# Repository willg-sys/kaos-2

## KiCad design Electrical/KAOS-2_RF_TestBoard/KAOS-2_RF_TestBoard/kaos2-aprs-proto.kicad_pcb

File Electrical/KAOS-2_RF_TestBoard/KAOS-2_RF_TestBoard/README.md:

# KAOS-2 RF Test Board (rev A)

Small 2-layer prototype (72 × 46 mm, 1.6 mm) to prove the 144.39 MHz APRS transmit chain and the 915 MHz LoRa link before the flight RF board. The RF MCU (Raspberry Pi Pico) stays off-board and connects through the 2×9 header J1.

## What's on it
- **144.39 MHz APRS TX:** Semtech SX1278 (direct-FSK AFSK from Pico PIO), Jauch 32 MHz TCXO, L-match to Semtech's measured PA_BOOST load (~13 + j7 Ω, AN1200.19), 7-pole 0.1 dB Chebyshev low-pass (fc ≈ 170 MHz), output pi-pad footprint, edge SMA (J3).
- **915 MHz LoRa:** Ai-Thinker Ra-01H (SX1276) with its own supply filter, pi-match footprint and a 50 Ω coplanar trace to edge SMA (J5).
- Bench 3.3 V input (J2) with current-measure jumper (JP1), test points, u.FL probe footprint (J4, DNP) between match and filter.

## Files
| File | What |
|---|---|
| `kaos2-aprs-proto.kicad_pro/.kicad_sch/.kicad_pcb` | KiCad project (KiCad 10 format) |
| `kaos2-aprs-proto.kicad_dru` | Custom DRC rule (KiCad 8+) waiving edge clearance for the edge-mount SMA pads |
| `fab/kaos2-rf-test_gerbers.zip` | Gerbers + drill exported from KiCad 10 (Protel extensions, single Excellon file) for OSH Park — or upload the `.kicad_pcb` directly |
| `fab/assembly_top.pdf` | Assembly drawing with all reference designators (generated before the KiCad 10 conversion; placement unchanged) |
| `fab/kaos2-aprs-proto_schematic.pdf` | Schematic PDF |

## Key values (144 MHz chain)
PA_BOOST → L4 33 nH series, C1 62 pF shunt; L5 220 nH choke to VR_PA (C8 100 nF at pin 25, C6 100 pF + C7 10 nF at the choke end) → DC block → 7-pole low-pass → pad (R2 0 Ω) → J3. Exact filter values are on the schematic. All RF caps C0G ±2 %; high-Q wire-wound inductors ±2 %.

## Firmware notes
- RegTcxo (0x4B) bit 4 TcxoInputOn = 1; XTB left open.
- Raise RegOcp from the 100 mA default to ~120–140 mA (PA draws ~87 mA at +17 dBm).
- NRESET / Ra-01H RESET must float at power-on (no pull-up): drive open-drain from the Pico.
- Never transmit on both radios at once. Pin assignments are in the J1 table on the schematic.

## Status / before ordering
- DRC (KiCad 10): 0 errors, 0 unconnected. Remaining warnings are expected: KiCad 7 footprint copies vs KiCad 10 library (do not update U1 from library — its thermal vias were enlarged to 0.3 mm drill for OSH Park), and local-label net naming (`RF_NODE` vs `/RF_NODE`).
- Do **not** run Update PCB from Schematic on this board: the footprint↔symbol links don't match and it scrambles placement.
- DNP: C0, C23, C24, J4, R1, R3, R4, R5, R11 (flags set on the board).
- Ra-01H footprint checked against Ai-Thinker's package drawing: 2.0 mm pitch, 8 pads/side, pin 1 (ANT) toward J5.
- Confirm OSH Park 2-layer minimums and dielectric constant (the 915 MHz trace is designed for εr ≈ 4.5).
- Bring-up: transmit only into a dummy load / 30 dB attenuator; measure power, current and harmonics (2nd, 3rd, 11th). Transmitting on 144.39 MHz requires a licensed operator and callsign.

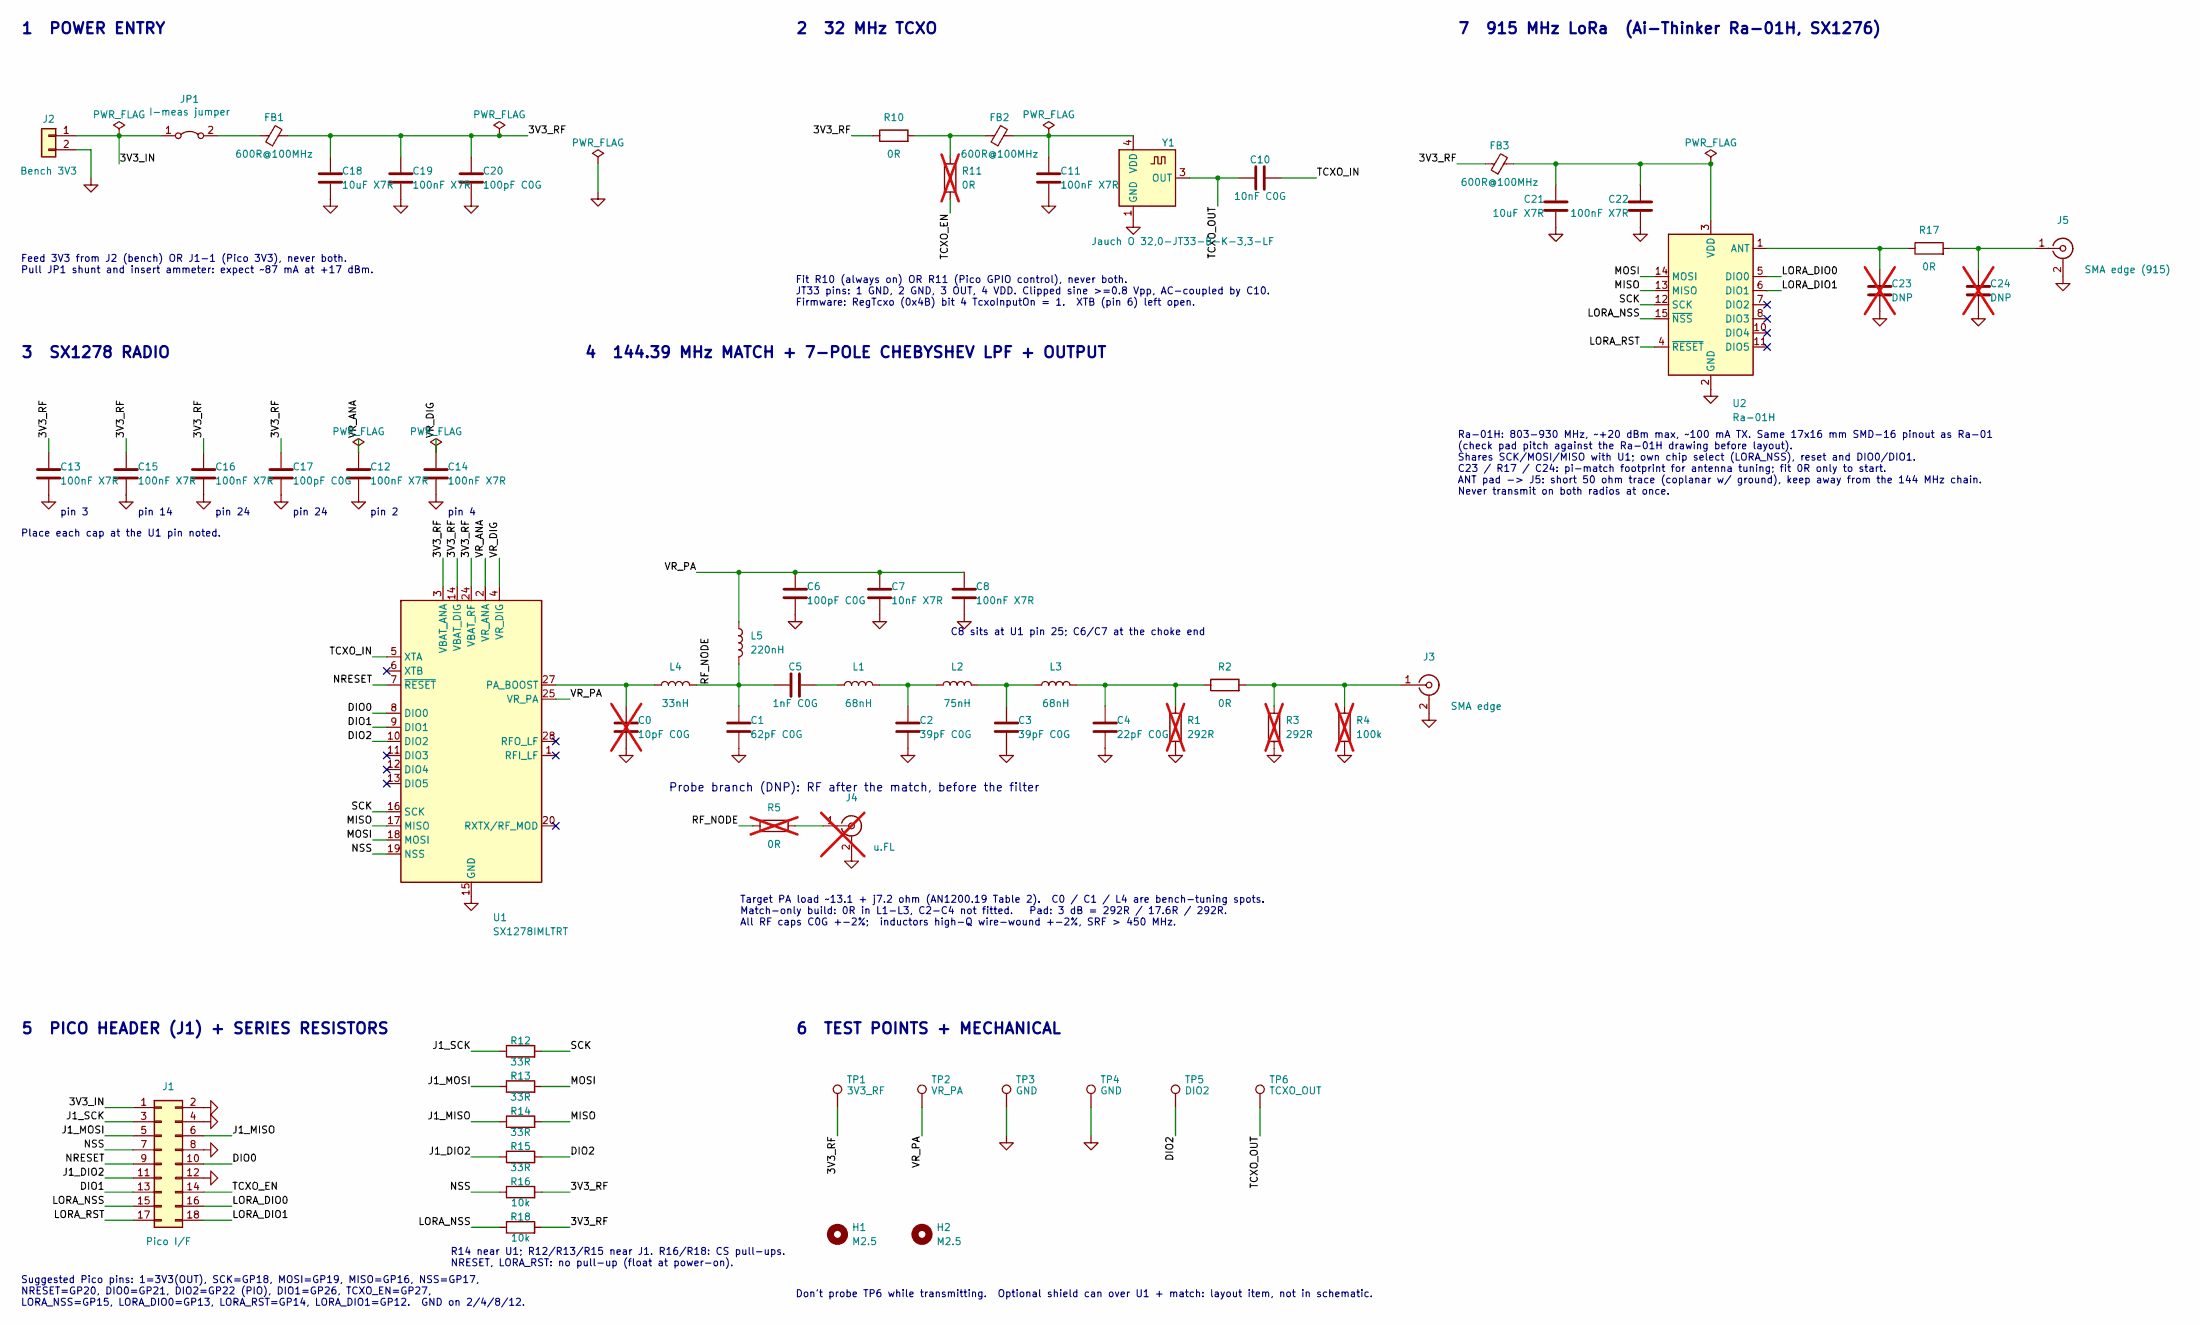
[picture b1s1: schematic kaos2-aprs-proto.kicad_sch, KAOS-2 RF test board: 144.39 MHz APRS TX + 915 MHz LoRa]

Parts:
C0: 10pF C0G; C_0603_1608Metric; not fitted
C1: 62pF C0G; C_0603_1608Metric
C2, C3: 39pF C0G; C_0603_1608Metric
C4: 22pF C0G; C_0603_1608Metric
C5: 1nF C0G; C_0603_1608Metric
C6, C17, C20: 100pF C0G; C_0603_1608Metric
C7: 10nF X7R; C_0603_1608Metric
C8, C11, C12, C13, C14, C15, C16, C19, C22: 100nF X7R; C_0603_1608Metric
C10: 10nF C0G; C_0603_1608Metric
C18, C21: 10uF X7R; C_0805_2012Metric
C23, C24: DNP; C_0603_1608Metric; not fitted
FB1, FB2, FB3: 600R@100MHz; L_0603_1608Metric
H1, H2: M2.5; MountingHole_2.7mm_M2.5
J1: Pico I/F; PinHeader_2x09_P2.54mm_Vertical
J2: Bench 3V3; PinHeader_1x02_P2.54mm_Vertical
J3: SMA edge; SMA_Samtec_SMA-J-P-X-ST-EM1_EdgeMount
J4: u.FL; U.FL_Hirose_U.FL-R-SMT-1_Vertical; not fitted
J5: SMA edge (915); SMA_Samtec_SMA-J-P-X-ST-EM1_EdgeMount
JP1: I-meas jumper; PinHeader_1x02_P2.54mm_Vertical
L1, L3: 68nH; L_0603_1608Metric
L2: 75nH; L_0603_1608Metric
L4: 33nH; L_0603_1608Metric
L5: 220nH; L_0603_1608Metric
R1, R3: 292R; R_0603_1608Metric; not fitted
R2, R10, R17: 0R; R_0603_1608Metric
R4: 100k; R_0603_1608Metric; not fitted
R5, R11: 0R; R_0603_1608Metric; not fitted
R12, R13, R14, R15: 33R; R_0603_1608Metric
R16, R18: 10k; R_0603_1608Metric
TP1: 3V3_RF; TestPoint_Pad_D1.0mm
TP2: VR_PA; TestPoint_Pad_D1.0mm
TP3, TP4: GND; TestPoint_Pad_D1.0mm
TP5: DIO2; TestPoint_Pad_D1.0mm
TP6: TCXO_OUT; TestPoint_Pad_D1.0mm
U1: SX1278IMLTRT; QFN-28-1EP_6x6mm_P0.65mm_EP4.8x4.8mm_ThermalVias
U2: Ra-01H; Ai-Thinker-Ra-01-LoRa
Y1: Jauch O 32,0-JT33-B-K-3,3-LF; Oscillator_SMD_Abracon_ASE-4Pin_3.2x2.5mm

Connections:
3V3_IN: J1.1, J2.1, JP1.1 (A)
3V3_RF: C13.1, C15.1, C16.1, C17.1, C18.1, C19.1, C20.1, FB1.2, FB3.1, R10.1, R16.2, R18.2, TP1.1, U1.3 (VBAT_ANA), U1.14 (VBAT_DIG), U1.24 (VBAT_RF)
DIO0: J1.10, U1.8 (DIO0)
DIO1: J1.13, U1.9 (DIO1)
DIO2: R15.2, TP5.1, U1.10 (DIO2)
GND: C0.2, C1.2, C2.2, C3.2, C4.2, C6.2, C7.2, C8.2, C11.2, C12.2, C13.2, C14.2, C15.2, C16.2, C17.2, C18.2, C19.2, C20.2, C21.2, C22.2, C23.2, C24.2, J1.2, J1.4, J1.8, J1.12, J2.2, J3.2 (Ext), J4.2 (Ext), J5.2 (Ext), R1.2, R3.2, R4.2, TP3.1, TP4.1, U1.15 (GND), U1.21 (GND), U1.22 (GND), U1.23 (GND), U1.26 (GND), U1.29 (GND), U2.2 (GND), U2.9 (GND), U2.16 (GND), Y1.1 (GND), Y1.2 (GND)
J1_DIO2: J1.11, R15.1
J1_MISO: J1.6, R14.1
J1_MOSI: J1.5, R13.1
J1_SCK: J1.3, R12.1
LORA_DIO0: J1.16, U2.5 (DIO0)
LORA_DIO1: J1.18, U2.6 (DIO1)
LORA_NSS: J1.15, R18.1, U2.15 (~NSS)
LORA_RST: J1.17, U2.4 (~RESET)
MISO: R14.2, U1.17 (MISO), U2.13 (MISO)
MOSI: R13.2, U1.18 (MOSI), U2.14 (MOSI)
NRESET: J1.9, U1.7 (~RESET)
NSS: J1.7, R16.1, U1.19 (NSS)
unnamed: C2.1, L1.2, L2.1
unnamed: C3.1, L2.2, L3.1
unnamed: C4.1, L3.2, R1.1, R2.1
unnamed: C5.2, L1.1
unnamed: FB2.1, R10.2, R11.1
unnamed: J3.1 (In), R2.2, R3.1, R4.1
unnamed: J4.1 (In), R5.2
unnamed: C24.1, J5.1 (In), R17.2
unnamed: FB1.1, JP1.2 (B)
unnamed: C0.1, L4.1, U1.27 (PA_BOOST)
unnamed: C23.1, R17.1, U2.1 (ANT)
unnamed: C21.1, C22.1, FB3.2, U2.3 (VDD)
unnamed: C11.1, FB2.2, Y1.4 (VDD)
RF_NODE: C1.1, C5.1, L4.2, L5.2, R5.1
SCK: R12.2, U1.16 (SCK), U2.12 (SCK)
TCXO_EN: J1.14, R11.2
TCXO_IN: C10.2, U1.5 (XTA)
TCXO_OUT: C10.1, TP6.1, Y1.3 (OUT)
VR_ANA: C12.1, U1.2 (VR_ANA)
VR_DIG: C14.1, U1.4 (VR_DIG)
VR_PA: C6.1, C7.1, C8.1, L5.1, TP2.1, U1.25 (VR_PA)

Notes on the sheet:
2 32 MHz TCXO
Don't probe TP6 while transmitting. Optional shield can over U1 + match: layout item, not in schematic.
pin 3
pin 24
pin 4
Fit R10 (always on) OR R11 (Pico GPIO control), never both. JT33 pins: 1 GND, 2 GND, 3 OUT, 4 VDD. Clipped sine >=0.8 Vpp, AC-coupled by C10. Firmware: RegTcxo (0x4B) bit 4 TcxoInputOn = 1. XTB (pin 6) left open.
Feed 3V3 from J2 (bench) OR J1-1 (Pico 3V3), never both. Pull JP1 shunt and insert ammeter: expect ~87 mA at +17 dBm.
pin 2
Target PA load ~13.1 + j7.2 ohm (AN1200.19 Table 2). C0 / C1 / L4 are bench-tuning spots. Match-only build: 0R in L1-L3, C2-C4 not fitted. Pad: 3 dB = 292R / 17.6R / 292R. All RF caps C0G +-2%; inductors high-Q wire-wound +-2%, SRF > 450 MHz.
Probe branch (DNP): RF after the match, before the filter
4 144.39 MHz MATCH + 7-POLE CHEBYSHEV LPF + OUTPUT
Suggested Pico pins: 1=3V3(OUT), SCK=GP18, MOSI=GP19, MISO=GP16, NSS=GP17, NRESET=GP20, DIO0=GP21, DIO2=GP22 (PIO), DIO1=GP26, TCXO_EN=GP27, LORA_NSS=GP15, LORA_DIO0=GP13, LORA_RST=GP14, LORA_DIO1=GP12. GND on 2/4/8/12.
C8 sits at U1 pin 25; C6/C7 at the choke end
6 TEST POINTS + MECHANICAL
3 SX1278 RADIO
Ra-01H: 803-930 MHz, ~+20 dBm max, ~100 mA TX. Same 17x16 mm SMD-16 pinout as Ra-01 (check pad pitch against the Ra-01H drawing before layout). Shares SCK/MOSI/MISO with U1; own chip select (LORA_NSS), reset and DIO0/DIO1. C23 / R17 / C24: pi-match footprint for antenna tuning; fit 0R only to start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
pin 14
1 POWER ENTRY
7 915 MHz LoRa (Ai-Thinker Ra-01H, SX1276)
R14 near U1; R12/R13/R15 near J1. R16/R18: CS pull-ups. NRESET, LORA_RST: no pull-up (float at power-on).
5 PICO HEADER (J1) + SERIES RESISTORS
Place each cap at the U1 pin noted.

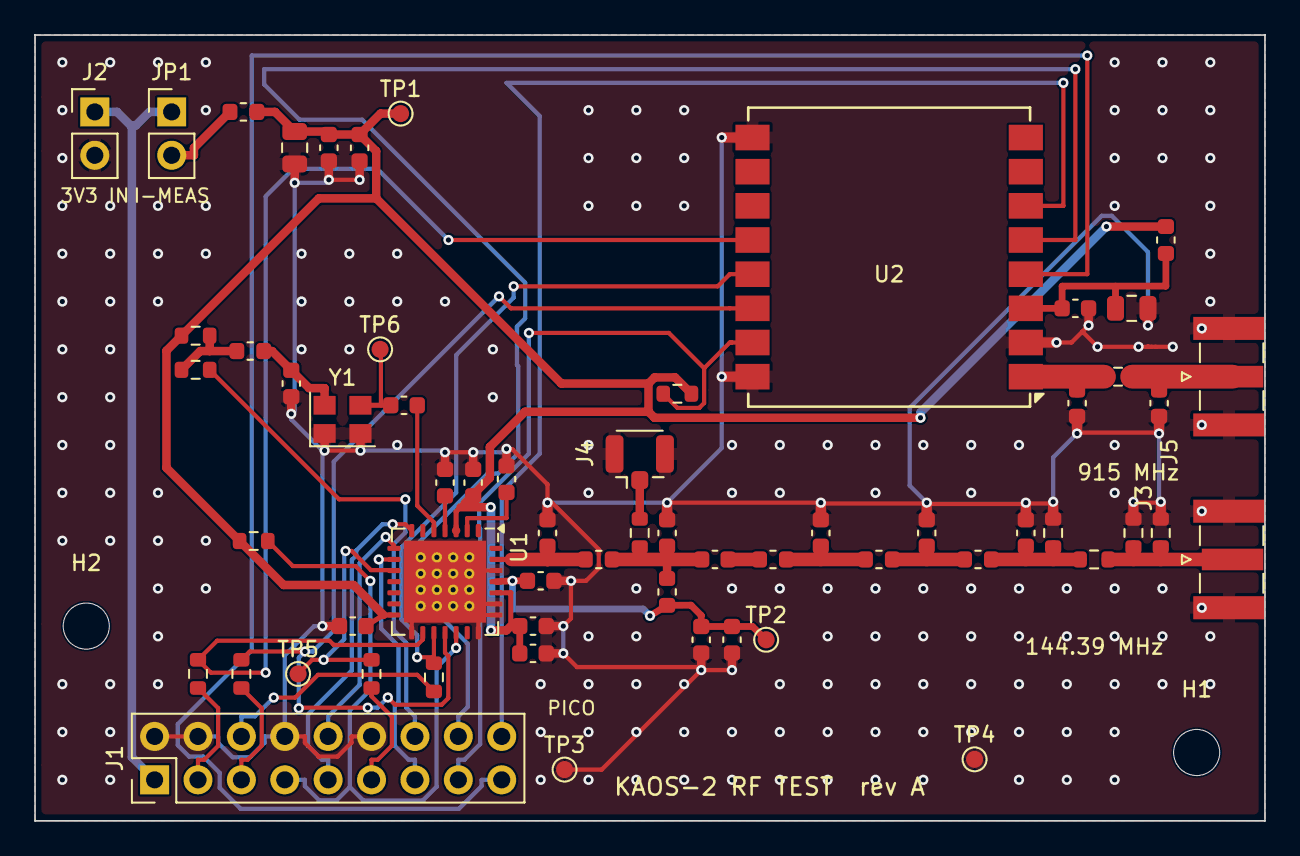
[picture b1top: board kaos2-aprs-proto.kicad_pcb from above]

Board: 2 copper layers, 72.0 x 46.0 mm, 63 parts (0 on the bottom side), 39 nets.
